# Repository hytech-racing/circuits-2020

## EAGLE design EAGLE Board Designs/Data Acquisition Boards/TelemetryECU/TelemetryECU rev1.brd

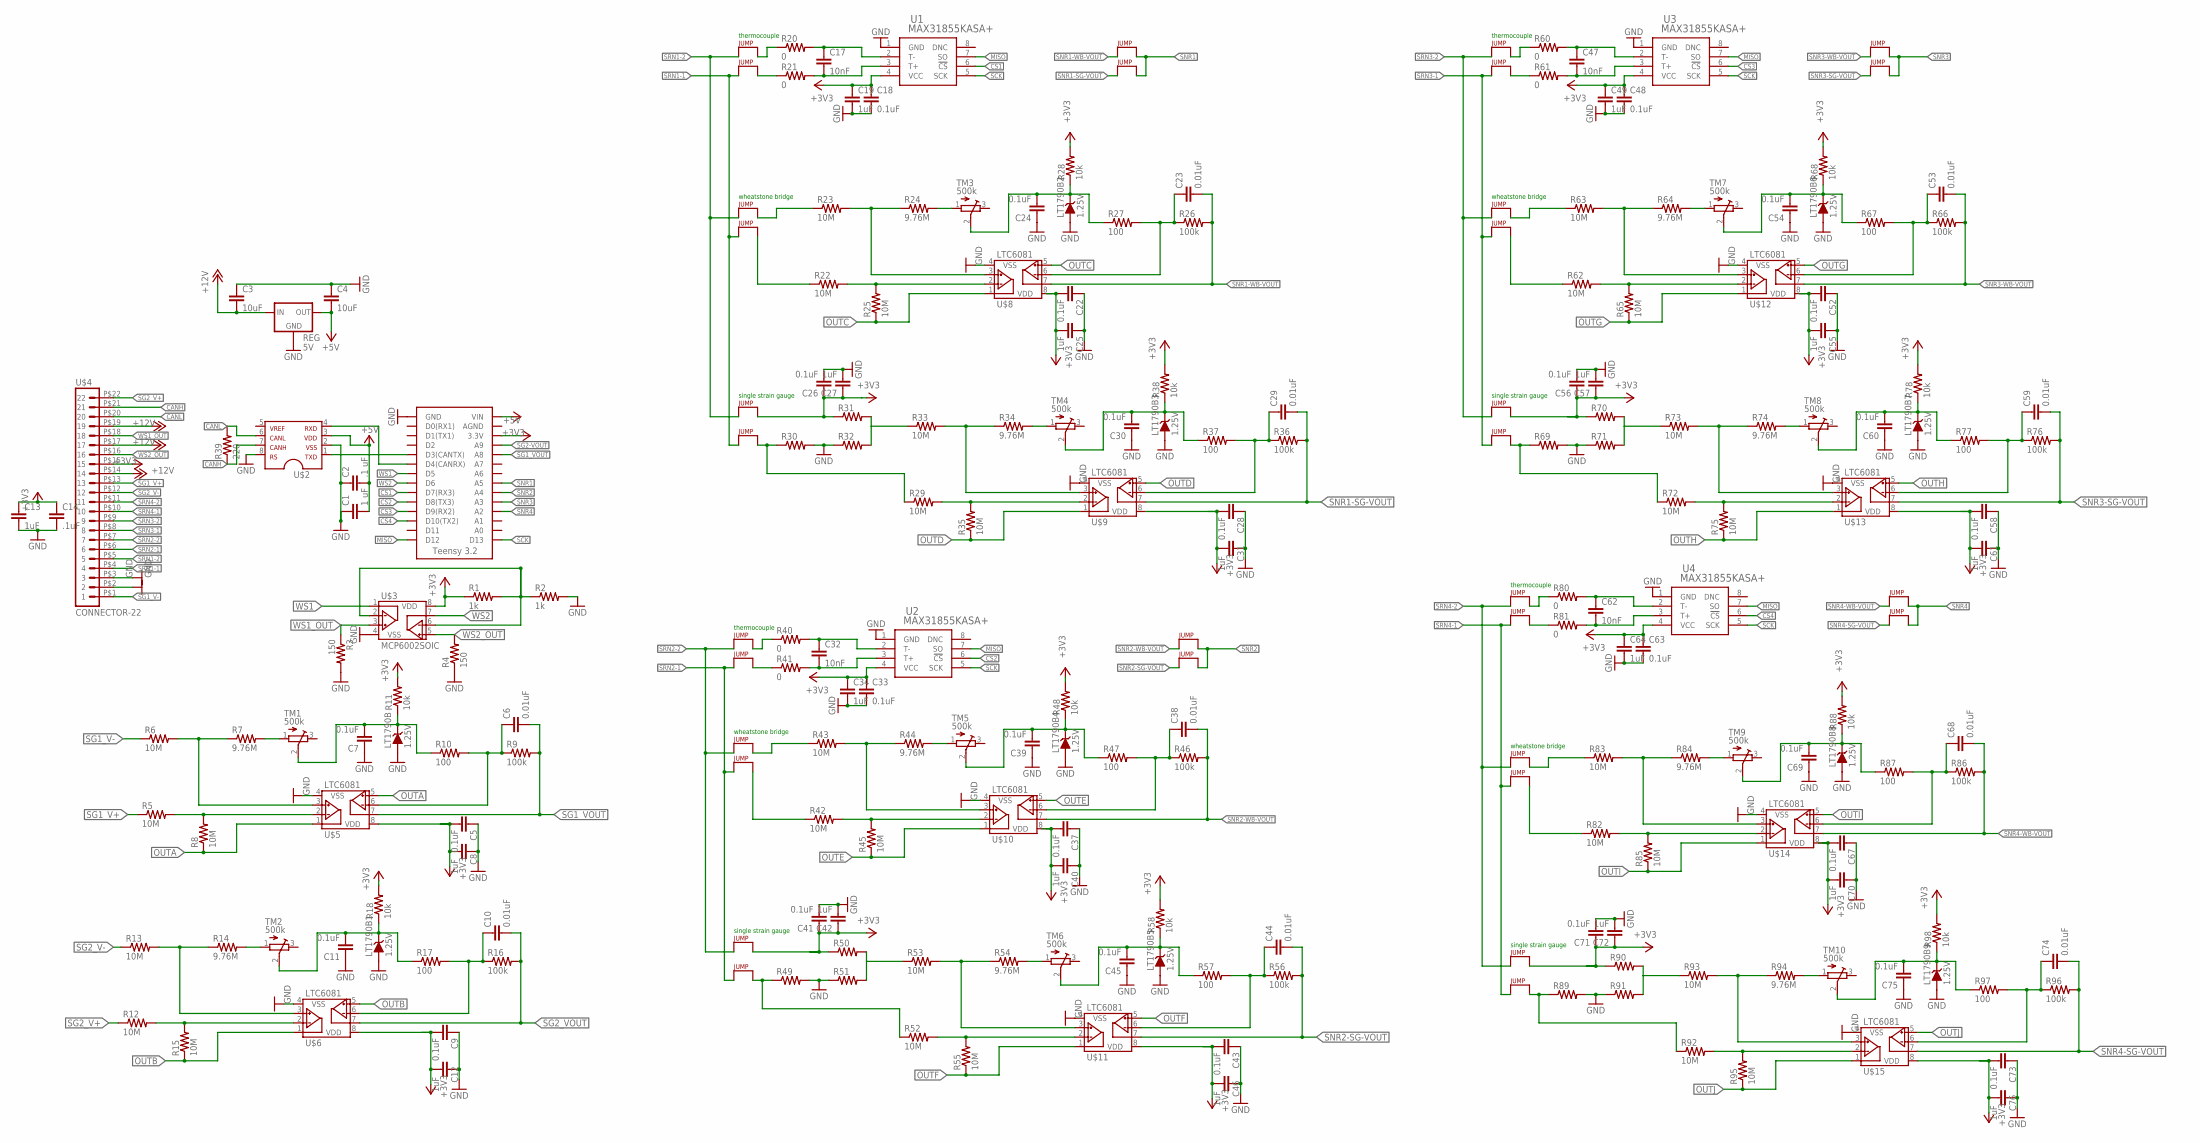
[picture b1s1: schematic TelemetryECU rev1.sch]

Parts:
C1: 1 uF; 0603-CAP
C2: .1 uF; 0603-CAP
C3, C4: 10uF; 0603-CAP
C5, C7, C9, C11, C18, C26, C33, C41, C48, C56, C63, C71: 0.1uF; 0603-CAP
C6, C10: 0.01uF; 0603-CAP
C8, C12, C13, C19, C27, C34, C42, C49, C57, C64, C72: 1uF; 0603-CAP
C14: .1uF; 0603-CAP
C17, C32, C47, C62: 10nF; 0603-CAP
C22, C24, C28, C30, C37, C39, C43, C45, C52, C54, C58, C60, C67, C69, C73, C75: 0.1uF; 0805
C23, C29, C38, C44, C53, C59, C68, C74: 0.01uF; 0805
C25, C31, C40, C46, C55, C61, C70, C76: 1uF; 0805
J1, J2, J5, J6, J7, J8, J9, J10, J13, J14, J15, J16, J17, J18, J21, J22, J23, J24, J25, J26, J29, J30, J31, J32, J34, J35, J37, J38, J40, J41, J42, J43: JUMPER.1; 1X02
LT1790B, LT1790B1, LT1790B2, LT1790B3, LT1790B4, LT1790B5, LT1790B6, LT1790B7, LT1790B8, LT1790B9: 1.25V; 0805_D
R1, R2: 1k; 0603-RES
R3, R4: 150; 0603-RES
R5, R6, R8, R12, R13, R15: 10M; 0603-RES
R7, R14: 9.76M; 0603-RES
R9, R16: 100k; 0603-RES
R10, R17: 100; 0603-RES
R11, R18: 10k; 0603-RES
R20, R21, R40, R41, R60, R61, R80, R81: 0; 0603-RES
R22, R23, R25, R29, R33, R35, R42, R43, R45, R52, R53, R55, R62, R63, R65, R72, R73, R75, R82, R83, R85, R92, R93, R95: 10M; 0805
R24, R34, R44, R54, R64, R74, R84, R94: 9.76M; 0805
R26, R36, R46, R56, R66, R76, R86, R96: 100k; 0805
R27, R37, R47, R57, R67, R77, R87, R97: 100; 0805
R28, R38, R48, R58, R68, R78, R88, R98: 10k; 0805
R30, R31, R32, R49, R50, R51, R69, R70, R71, R89, R90, R91: RESISTOR0603; 0603-RES
R39: 220; 0603-RES
REG: 5V; OKI-78SR
TM1, TM2, TM3, TM4, TM5, TM6, TM7, TM8, TM9, TM10: 500k; TC33X
U1, U2, U3, U4: MAX31855KASA+; 21-0041B_8
U$1: TEENSY_3.2_SIMPLE
U$2: MCP2551; SOIC-08
U$3: MCP6002SOIC; SOIC-08
U$4: CONNECTOR-22; AUTOSPORT_12-35
U$5, U$6, U$8, U$9, U$10, U$11, U$12, U$13, U$14, U$15: LTC6081; MSOP-8_MS

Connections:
+3V3: C5.2, C8.1, C9.2, C12.1, C13.1, C14.1, C18.1, C19.1, C22.2, C25.2, C26.1, C27.1, C28.2, C31.1, C33.1, C34.1, C37.2, C40.2, C41.1, C42.1, C43.2, C46.1, C48.1, C49.1, C52.2, C55.2, C56.1, C57.1, C58.2, C61.1, C63.1, C64.1, C67.2, C70.2, C71.1, C72.1, C73.2, C76.1, J7.2, J15.2, J23.2, J31.2, R1.1, R11.2, R18.2, R28.2, R31.1, R38.2, R48.2, R50.1, R58.2, R68.2, R70.1, R78.2, R88.2, R90.1, R98.2, U1.4 (VCC), U2.4 (VCC), U3.4 (VCC), U4.4 (VCC), U$1.3.3V, U$3.8 (VDD), U$4.P$15 (15), U$5.8 (VDD), U$6.8 (VDD), U$8.8 (VDD), U$9.8 (VDD), U$10.8 (VDD), U$11.8 (VDD), U$12.8 (VDD), U$13.8 (VDD), U$14.8 (VDD), U$15.8 (VDD)
+5V: C1.2, C2.2, C4.2, REG.3 (OUT), U$1.VIN, U$2.3
+12V: C3.2, REG.1 (IN), U$4.P$14 (14), U$4.P$17 (17), U$4.P$19 (19)
CANH: R39.1, U$2.7, U$4.P$21 (21)
CANL: R39.2, U$2.6, U$4.P$20 (20)
CS1: U1.6 (!CS), U$1.D7(RX3)
CS2: U2.6 (!CS), U$1.D8(TX3)
CS3: U3.6 (!CS), U$1.D9(RX2)
CS4: U4.6 (!CS), U$1.D10(TX2)
GND: C1.1, C2.1, C3.1, C4.1, C5.1, C7.1, C8.2, C9.1, C11.1, C12.2, C13.2, C14.2, C18.2, C19.2, C22.1, C24.1, C25.1, C26.2, C27.2, C28.1, C30.1, C31.2, C33.2, C34.2, C37.1, C39.1, C40.1, C41.2, C42.2, C43.1, C45.1, C46.2, C48.2, C49.2, C52.1, C54.1, C55.1, C56.2, C57.2, C58.1, C60.1, C61.2, C63.2, C64.2, C67.1, C69.1, C70.1, C71.2, C72.2, C73.1, C75.1, C76.2, LT1790B.A, LT1790B1.A, LT1790B2.A, LT1790B3.A, LT1790B4.A, LT1790B5.A, LT1790B6.A, LT1790B7.A, LT1790B8.A, LT1790B9.A, R2.2, R3.2, R4.1, R30.2, R32.1, R49.2, R51.1, R69.2, R71.1, R89.2, R91.1, REG.2 (GND), U1.1 (GND), U2.1 (GND), U3.1 (GND), U4.1 (GND), U$1.GND, U$2.2, U$2.8, U$3.4 (VSS), U$4.P$2 (2), U$4.P$3 (3), U$5.4 (VSS), U$6.4 (VSS), U$8.4 (VSS), U$9.4 (VSS), U$10.4 (VSS), U$11.4 (VSS), U$12.4 (VSS), U$13.4 (VSS), U$14.4 (VSS), U$15.4 (VSS)
INB-: C6.1, R9.1, R10.2, U$5.6 (VINB-)
INB-1: C10.1, R16.1, R17.2, U$6.6 (VINB-)
INB-2: C23.1, R26.1, R27.2, U$8.6 (VINB-)
INB-3: C29.1, R36.1, R37.2, U$9.6 (VINB-)
INB-4: C38.1, R46.1, R47.2, U$10.6 (VINB-)
INB-5: C44.1, R56.1, R57.2, U$11.6 (VINB-)
INB-6: C53.1, R66.1, R67.2, U$12.6 (VINB-)
INB-7: C59.1, R76.1, R77.2, U$13.6 (VINB-)
INB-8: C68.1, R86.1, R87.2, U$14.6 (VINB-)
INB-9: C74.1, R96.1, R97.2, U$15.6 (VINB-)
MISO: U1.7 (SO), U2.7 (SO), U3.7 (SO), U4.7 (SO), U$1.D12
unnamed: U$1.D4(CANRX), U$2.4
unnamed: C17.1, R20.2, U1.2 (T-)
unnamed: U$1.D3(CANTX), U$2.1
unnamed: R1.2, R2.1, U$3.2 (VINA-), U$3.6 (VINB-)
unnamed: R5.2, R8.2, U$5.2 (VINA-)
unnamed: C17.2, R21.2, U1.3 (T+)
unnamed: J2.2, R21.1
unnamed: R6.2, R7.1, U$5.3 (VINA+)
unnamed: C7.2, LT1790B.C, R10.1, R11.1, TM1.2 (S)
unnamed: R7.2, TM1.1 (A)
unnamed: R12.2, R15.2, U$6.2 (VINA-)
unnamed: R13.2, R14.1, U$6.3 (VINA+)
unnamed: C11.2, LT1790B1.C, R17.1, R18.1, TM2.2 (S)
unnamed: R14.2, TM2.1 (A)
unnamed: J1.2, R20.1
unnamed: R22.2, R25.2, U$8.2 (VINA-)
unnamed: R23.2, R24.1, U$8.3 (VINA+)
unnamed: C24.2, LT1790B2.C, R27.1, R28.1, TM3.2 (S)
unnamed: R24.2, TM3.1 (A)
unnamed: J6.2, R22.1
unnamed: R31.2, R32.2, R33.1
unnamed: J8.2, R29.1, R30.1
unnamed: C32.1, R40.2, U2.2 (T-)
unnamed: J5.2, R23.1
unnamed: R29.2, R35.2, U$9.2 (VINA-)
unnamed: R33.2, R34.1, U$9.3 (VINA+)
unnamed: C30.2, LT1790B3.C, R37.1, R38.1, TM4.2 (S)
unnamed: R34.2, TM4.1 (A)
unnamed: C32.2, R41.2, U2.3 (T+)
unnamed: J10.2, R41.1
unnamed: J9.2, R40.1
unnamed: R42.2, R45.2, U$10.2 (VINA-)
unnamed: R43.2, R44.1, U$10.3 (VINA+)
unnamed: C39.2, LT1790B4.C, R47.1, R48.1, TM5.2 (S)
unnamed: R44.2, TM5.1 (A)
unnamed: R50.2, R51.2, R53.1
unnamed: J16.2, R49.1, R52.1
unnamed: J14.2, R42.1
unnamed: J13.2, R43.1
unnamed: R52.2, R55.2, U$11.2 (VINA-)
unnamed: R53.2, R54.1, U$11.3 (VINA+)
unnamed: C45.2, LT1790B5.C, R57.1, R58.1, TM6.2 (S)
unnamed: R54.2, TM6.1 (A)
unnamed: C47.1, R60.2, U3.2 (T-)
unnamed: C47.2, R61.2, U3.3 (T+)
unnamed: J18.2, R61.1
unnamed: J17.2, R60.1
unnamed: R62.2, R65.2, U$12.2 (VINA-)
unnamed: R63.2, R64.1, U$12.3 (VINA+)
unnamed: C54.2, LT1790B6.C, R67.1, R68.1, TM7.2 (S)
unnamed: R64.2, TM7.1 (A)
unnamed: R70.2, R71.2, R73.1
unnamed: J24.2, R69.1, R72.1
unnamed: J22.2, R62.1
unnamed: J21.2, R63.1
unnamed: R72.2, R75.2, U$13.2 (VINA-)
unnamed: R73.2, R74.1, U$13.3 (VINA+)
unnamed: C60.2, LT1790B7.C, R77.1, R78.1, TM8.2 (S)
unnamed: R74.2, TM8.1 (A)
unnamed: C62.1, R80.2, U4.2 (T-)
unnamed: C62.2, R81.2, U4.3 (T+)
unnamed: J26.2, R81.1
unnamed: J25.2, R80.1
unnamed: R82.2, R85.2, U$14.2 (VINA-)
unnamed: R83.2, R84.1, U$14.3 (VINA+)
unnamed: C69.2, LT1790B8.C, R87.1, R88.1, TM9.2 (S)
unnamed: R84.2, TM9.1 (A)
unnamed: R90.2, R91.2, R93.1
unnamed: J32.2, R89.1, R92.1
unnamed: J30.2, R82.1
unnamed: J29.2, R83.1
unnamed: R92.2, R95.2, U$15.2 (VINA-)
unnamed: R93.2, R94.1, U$15.3 (VINA+)
unnamed: C75.2, LT1790B9.C, R97.1, R98.1, TM10.2 (S)
unnamed: R94.2, TM10.1 (A)
OUTA: R8.1, U$5.1 (VOUTA), U$5.5 (VINB+)
OUTB: R15.1, U$6.1 (VOUTA), U$6.5 (VINB+)
OUTC: R25.1, U$8.1 (VOUTA), U$8.5 (VINB+)
OUTD: R35.1, U$9.1 (VOUTA), U$9.5 (VINB+)
OUTE: R45.1, U$10.1 (VOUTA), U$10.5 (VINB+)
OUTF: R55.1, U$11.1 (VOUTA), U$11.5 (VINB+)
OUTG: R65.1, U$12.1 (VOUTA), U$12.5 (VINB+)
OUTH: R75.1, U$13.1 (VOUTA), U$13.5 (VINB+)
OUTI: R85.1, U$14.1 (VOUTA), U$14.5 (VINB+)
OUTJ: R95.1, U$15.1 (VOUTA), U$15.5 (VINB+)
SCK: U1.5 (SCK), U2.5 (SCK), U3.5 (SCK), U4.5 (SCK), U$1.D13
SG1_V+: R5.1, U$4.P$13 (13)
SG1_V-: R6.1, U$4.P$1 (1)
SG1_VOUT: C6.2, R9.2, U$1.A8, U$5.7 (VOUTB)
SG2-VOUT: U$1.A9
SG2_V+: R12.1, U$4.P$22 (22)
SG2_V-: R13.1, U$4.P$12 (12)
SG2_VOUT: C10.2, R16.2, U$6.7 (VOUTB)
SNR1: J34.2, J35.2, U$1.A5
SNR1-SG-VOUT: C29.2, J35.1, R36.2, U$9.7 (VOUTB)
SNR1-WB-VOUT: C23.2, J34.1, R26.2, U$8.7 (VOUTB)
SNR2: J42.2, J43.2, U$1.A4
SNR2-SG-VOUT: C44.2, J42.1, R56.2, U$11.7 (VOUTB)
SNR2-WB-VOUT: C38.2, J43.1, R46.2, U$10.7 (VOUTB)
SNR3: J37.2, J38.2, U$1.A3
SNR3-SG-VOUT: C59.2, J38.1, R76.2, U$13.7 (VOUTB)
SNR3-WB-VOUT: C53.2, J37.1, R66.2, U$12.7 (VOUTB)
SNR4: J40.2, J41.2, U$1.A2
SNR4-SG-VOUT: C74.2, J41.1, R96.2, U$15.7 (VOUTB)
SNR4-WB-VOUT: C68.2, J40.1, R86.2, U$14.7 (VOUTB)
SRN1-1: J2.1, J6.1, J8.1, U$4.P$4 (4)
SRN1-2: J1.1, J5.1, J7.1, U$4.P$5 (5)
SRN2-1: J10.1, J14.1, J16.1, U$4.P$6 (6)
SRN2-2: J9.1, J13.1, J15.1, U$4.P$7 (7)
SRN3-1: J18.1, J22.1, J24.1, U$4.P$8 (8)
SRN3-2: J17.1, J21.1, J23.1, U$4.P$9 (9)
SRN4-1: J26.1, J30.1, J32.1, U$4.P$10 (10)
SRN4-2: J25.1, J29.1, J31.1, U$4.P$11 (11)
WS1: U$1.D5, U$3.1 (VOUTA)
WS1_OUT: R3.1, U$3.3 (VINA+), U$4.P$18 (18)
WS2: U$1.D6, U$3.7 (VOUTB)
WS2_OUT: R4.2, U$3.5 (VINB+), U$4.P$16 (16)

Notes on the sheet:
thermocouple
wheatstone bridge
single strain gauge

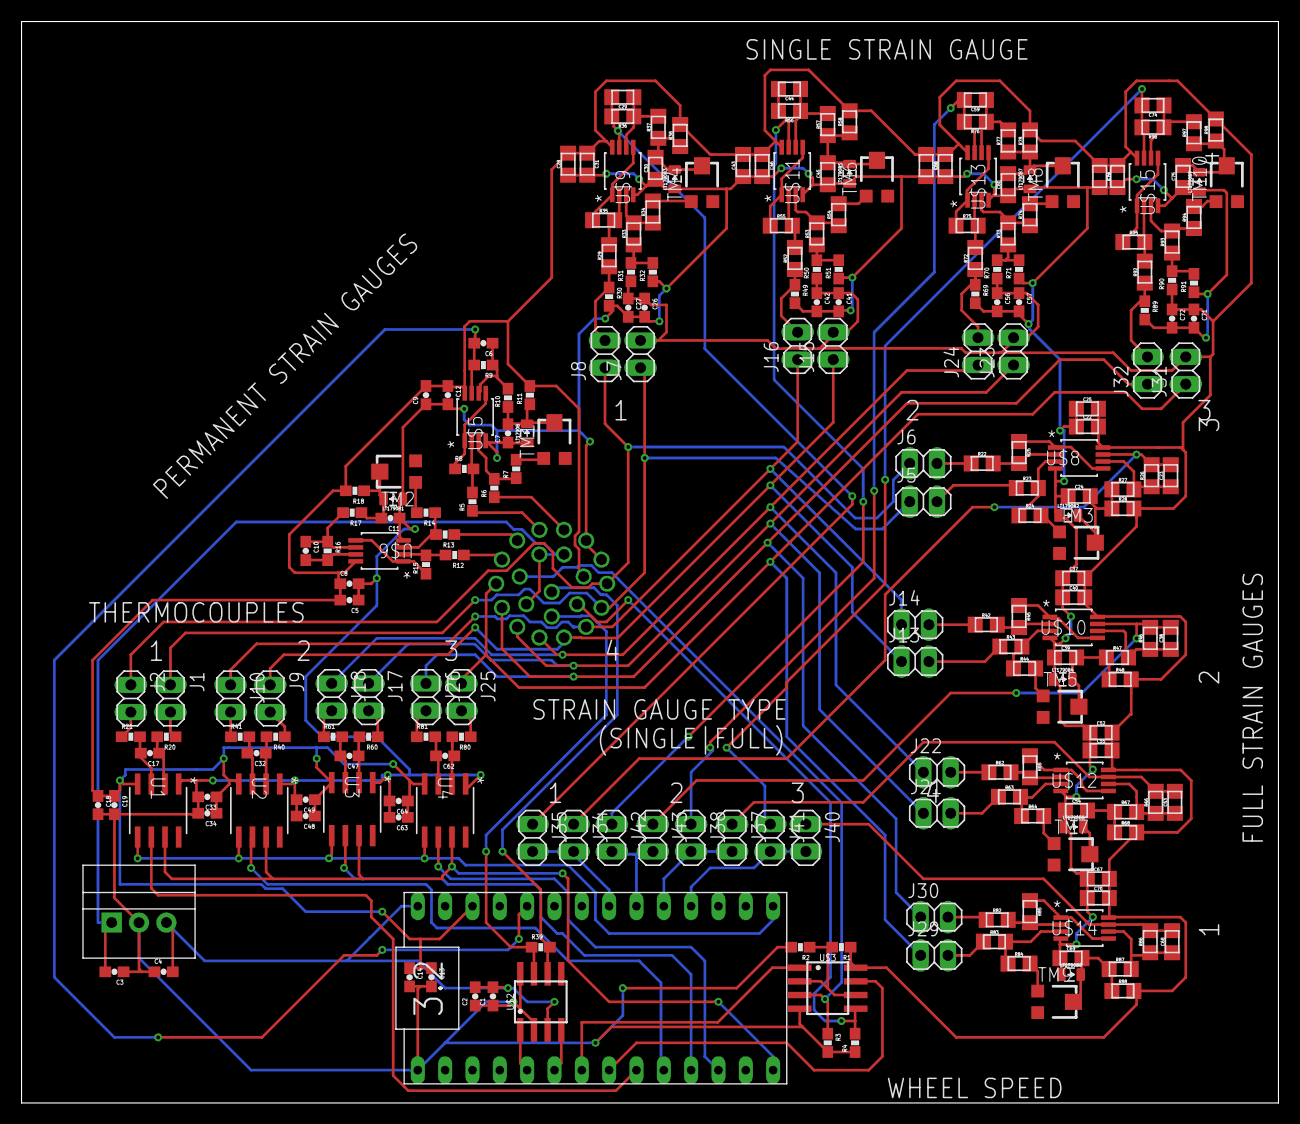
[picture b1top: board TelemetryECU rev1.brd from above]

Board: 2 copper layers, 116.8 x 100.5 mm, 232 parts (0 on the bottom side), 137 nets.

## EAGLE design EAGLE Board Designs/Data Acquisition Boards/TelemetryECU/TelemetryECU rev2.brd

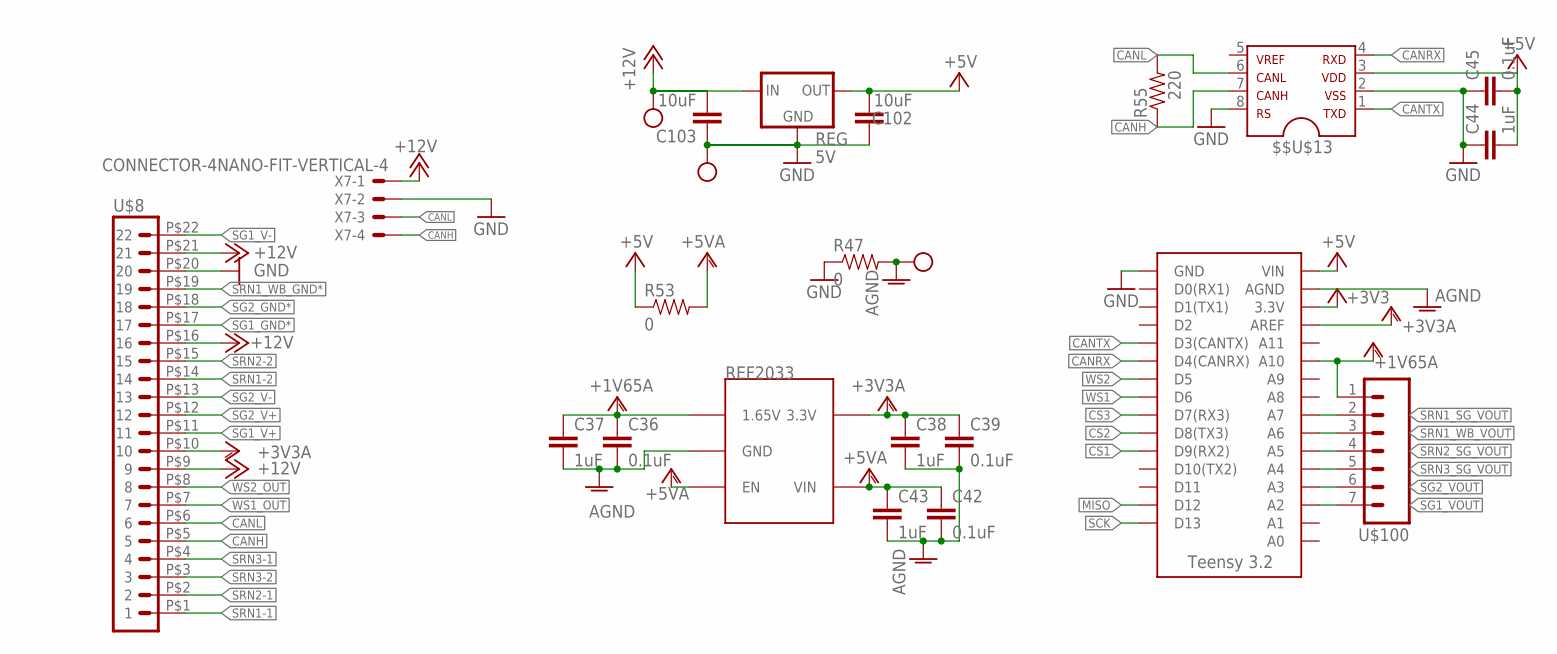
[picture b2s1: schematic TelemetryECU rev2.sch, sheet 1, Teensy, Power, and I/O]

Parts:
$$U$11: TEST_POINT
$$U$13: MCP2551; SOIC-08
C36, C39, C42, C45: 0.1uF; 0603-CAP
C37, C38, C43, C44: 1uF; 0603-CAP
C102, C103: 10uF; 0603-CAP
R47, R53: 0; 0603-RES
R55: 220; 0603-RES
REG: 5V; OKI-78SR
U$7: REF2033; SOT-23-5
U$8: CONNECTOR-22; AUTOSPORT_12-35
U$9, U$10: TEST_POINT
U$14: TEENSY_3.2_EXT_12ANALOG_AREF
U$100: M07; 1X07
X7: CONNECTOR-4NANO-FIT-VERTICAL-4; NANO-FIT_VERTICAL-4

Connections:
+1V65A: C36.1, C37.1, U$7.1 (1.65V), U$14.A10, U$100.1; also elsewhere on the board
+3V3: U$14.3.3V; also elsewhere on the board
+3V3A: C38.1, C39.1, U$7.5 (3.3V), U$8.P$10 (10), U$14.AREF; also elsewhere on the board
+5V: $$U$13.3, C44.2, C45.2, C102.2, R53.1, REG.3 (OUT), U$14.VIN
+5VA: C42.1, C43.1, R53.2, U$7.3 (EN), U$7.4 (VIN); also elsewhere on the board
+12V: C103.2, REG.1 (IN), U$8.P$9 (9), U$8.P$16 (16), U$8.P$21 (21), U$10.P$1, X7.P$1
AGND: $$U$11.P$1, C36.2, C37.2, C38.2, C39.2, C42.2, C43.2, R47.2, U$7.2 (GND), U$14.AGND; also elsewhere on the board
CANH: $$U$13.7, R55.1, U$8.P$5 (5), X7.P$4
CANL: $$U$13.6, R55.2, U$8.P$6 (6), X7.P$3
CANRX: $$U$13.4, U$14.D4(CANRX)
CANTX: $$U$13.1, U$14.D3(CANTX)
CS1: U$14.D9(RX2); also elsewhere on the board
CS2: U$14.D8(TX3); also elsewhere on the board
CS3: U$14.D7(RX3); also elsewhere on the board
GND: $$U$13.2, $$U$13.8, C44.1, C45.1, C102.1, C103.1, R47.1, REG.2 (GND), U$8.P$20 (20), U$9.P$1, U$14.GND, X7.P$2; also elsewhere on the board
MISO: U$14.D12; also elsewhere on the board
SCK: U$14.D13; also elsewhere on the board
SG1_GND*: U$8.P$17 (17); also elsewhere on the board
SG1_V+: U$8.P$11 (11); also elsewhere on the board
SG1_V-: U$8.P$22 (22); also elsewhere on the board
SG1_VOUT: U$14.A2, U$100.7; also elsewhere on the board
SG2_GND*: U$8.P$18 (18); also elsewhere on the board
SG2_V+: U$8.P$12 (12); also elsewhere on the board
SG2_V-: U$8.P$13 (13); also elsewhere on the board
SG2_VOUT: U$14.A3, U$100.6; also elsewhere on the board
SRN1-1: U$8.P$1 (1); also elsewhere on the board
SRN1-2: U$8.P$14 (14); also elsewhere on the board
SRN1_SG_VOUT: U$14.A7, U$100.2; also elsewhere on the board
SRN1_WB_GND*: U$8.P$19 (19); also elsewhere on the board
SRN1_WB_VOUT: U$14.A6, U$100.3; also elsewhere on the board
SRN2-1: U$8.P$2 (2); also elsewhere on the board
SRN2-2: U$8.P$15 (15); also elsewhere on the board
SRN2_SG_VOUT: U$14.A5, U$100.4; also elsewhere on the board
SRN3-1: U$8.P$4 (4); also elsewhere on the board
SRN3-2: U$8.P$3 (3); also elsewhere on the board
SRN3_SG_VOUT: U$14.A4, U$100.5; also elsewhere on the board
WS1: U$14.D6; also elsewhere on the board
WS1_OUT: U$8.P$7 (7); also elsewhere on the board
WS2: U$14.D5; also elsewhere on the board
WS2_OUT: U$8.P$8 (8); also elsewhere on the board

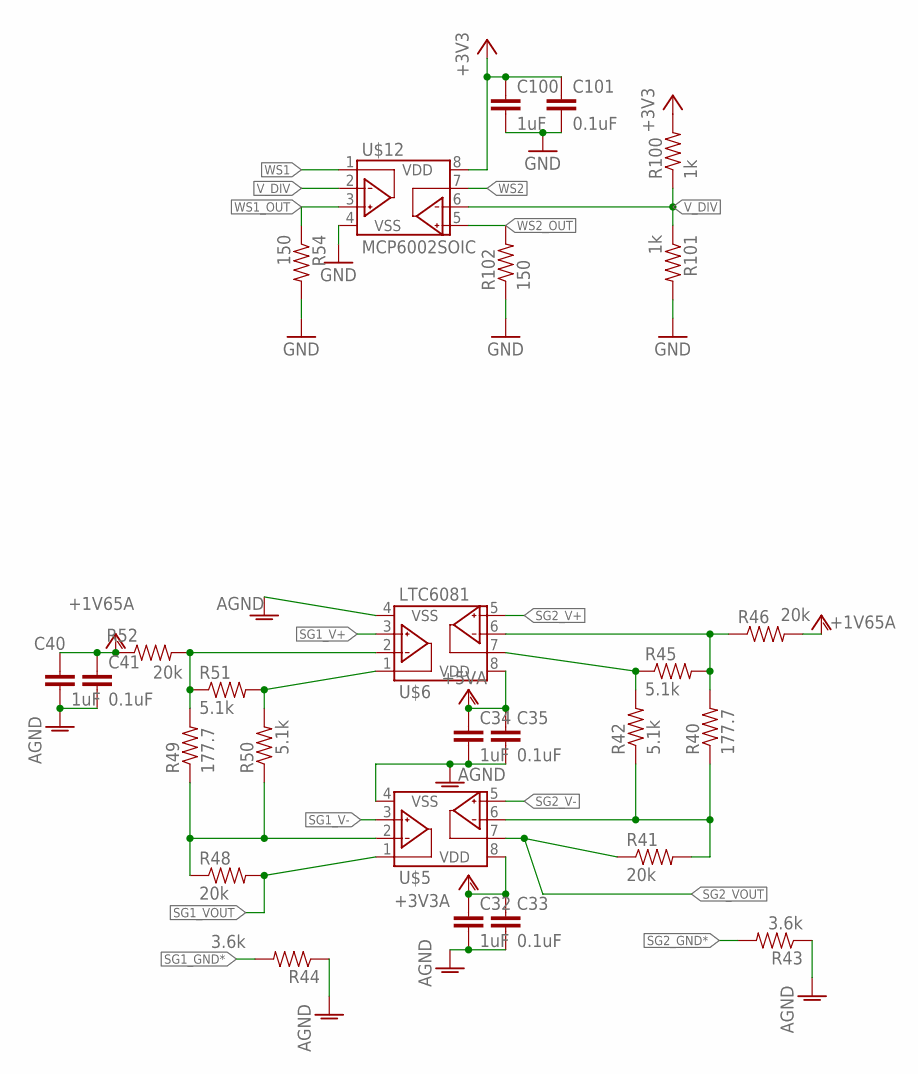
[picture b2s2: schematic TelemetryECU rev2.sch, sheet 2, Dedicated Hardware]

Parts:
C32, C34, C40, C100: 1uF; 0603-CAP
C33, C35, C41, C101: 0.1uF; 0603-CAP
R40, R49: 177.7; 0603-RES
R41, R46, R48, R52: 20k; 0603-RES
R42, R45, R50, R51: 5.1k; 0603-RES
R43, R44: 3.6k; 0603-RES
R54, R102: 150; 0603-RES
R100, R101: 1k; 0603-RES
U$5, U$6: LTC6081; MSOP-8_MS
U$12: MCP6002SOIC; SOIC-08

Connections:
+1V65A: C40.1, C41.1, R46.2, R52.1; also elsewhere on the board
+3V3: C100.1, C101.1, R100.2, U$12.8 (VDD); also elsewhere on the board
+3V3A: C32.1, C33.1, U$5.8 (VDD); also elsewhere on the board
+5VA: C34.1, C35.1, U$6.8 (VDD); also elsewhere on the board
AGND: C32.2, C33.2, C34.2, C35.2, C40.2, C41.2, R43.1, R44.1, U$5.4 (VSS), U$6.4 (VSS); also elsewhere on the board
GND: C100.2, C101.2, R54.2, R101.2, R102.1, U$12.4 (VSS); also elsewhere on the board
unnamed: R50.2, R51.2, U$6.1 (VOUTA)
unnamed: R49.2, R51.1, R52.2, U$6.2 (VINA-)
unnamed: R40.2, R45.2, R46.1, U$6.6 (VINB-)
unnamed: R48.1, R49.1, R50.1, U$5.2 (VINA-)
unnamed: R42.2, R45.1, U$6.7 (VOUTB)
unnamed: R40.1, R41.2, R42.1, U$5.6 (VINB-)
SG1_GND*: R44.2; also elsewhere on the board
SG1_V+: U$6.3 (VINA+); also elsewhere on the board
SG1_V-: U$5.3 (VINA+); also elsewhere on the board
SG1_VOUT: R48.2, U$5.1 (VOUTA); also elsewhere on the board
SG2_GND*: R43.2; also elsewhere on the board
SG2_V+: U$6.5 (VINB+); also elsewhere on the board
SG2_V-: U$5.5 (VINB+); also elsewhere on the board
SG2_VOUT: R41.1, U$5.7 (VOUTB); also elsewhere on the board
V_DIV: R100.1, R101.1, U$12.2 (VINA-), U$12.6 (VINB-)
WS1: U$12.1 (VOUTA); also elsewhere on the board
WS1_OUT: R54.1, U$12.3 (VINA+); also elsewhere on the board
WS2: U$12.7 (VOUTB); also elsewhere on the board
WS2_OUT: R102.2, U$12.5 (VINB+); also elsewhere on the board

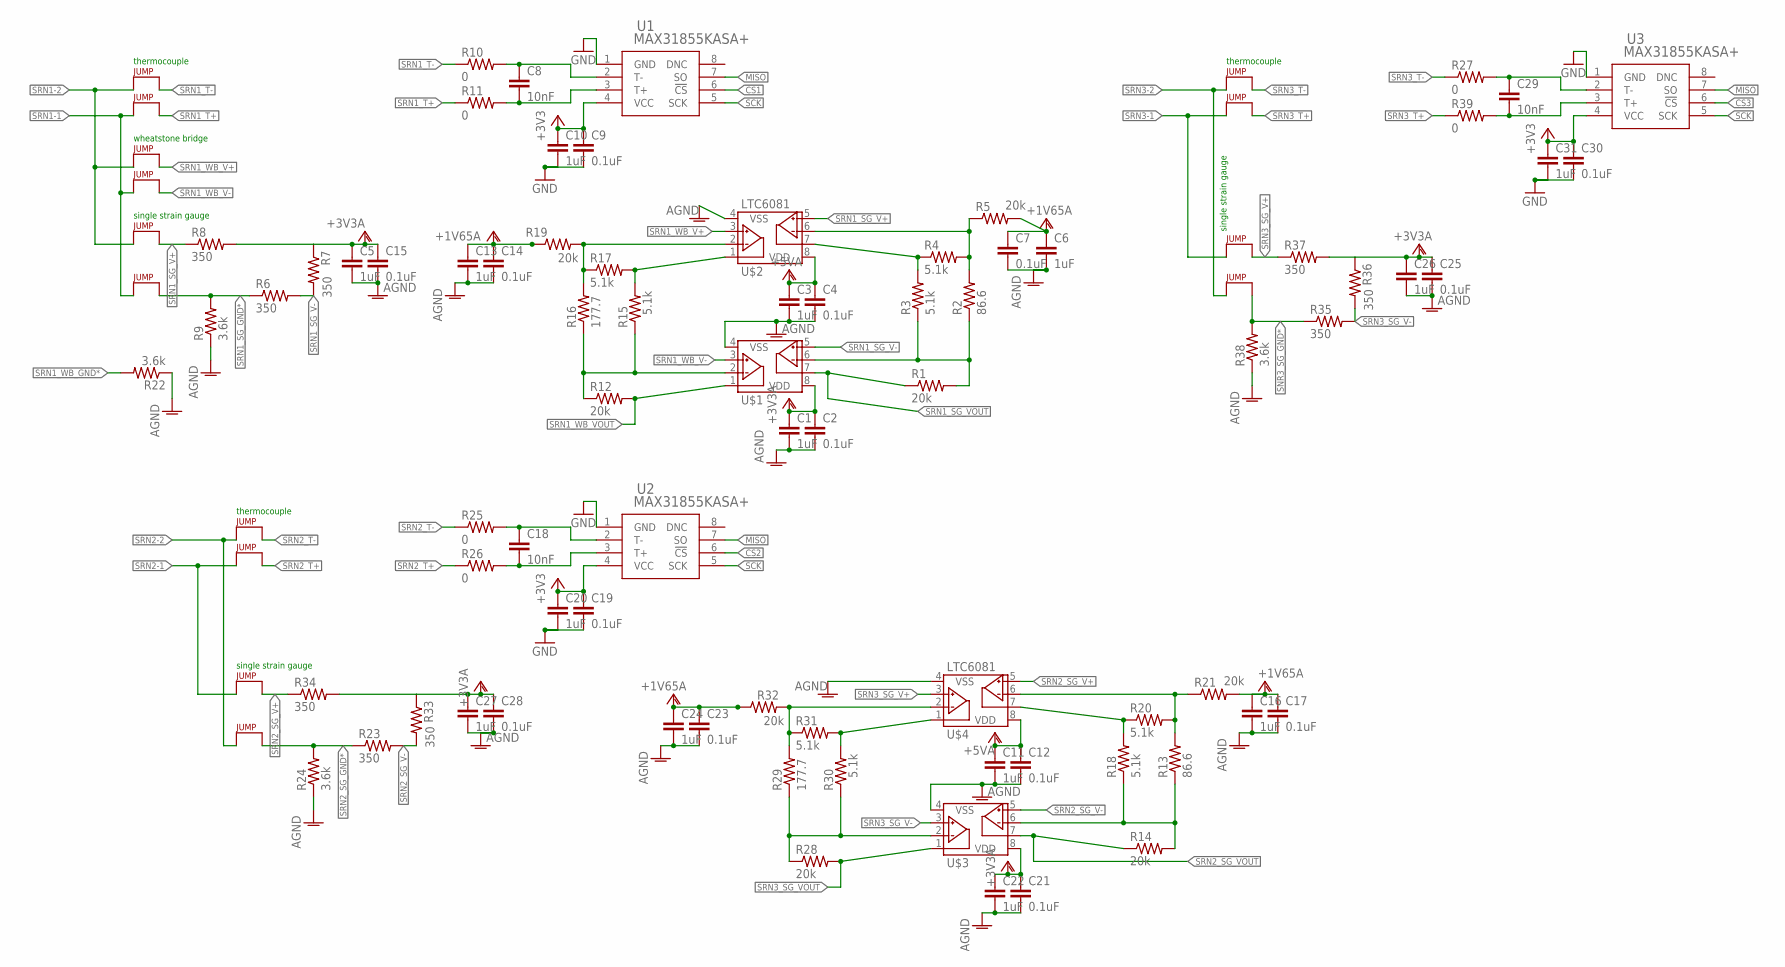
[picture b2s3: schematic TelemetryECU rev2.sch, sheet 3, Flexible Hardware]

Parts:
C1, C3, C5, C6, C10, C11, C13, C16, C20, C22, C24, C26, C27, C31: 1uF; 0603-CAP
C2, C4, C7, C9, C12, C14, C15, C17, C19, C21, C23, C25, C28, C30: 0.1uF; 0603-CAP
C8, C18, C29: 10nF; 0603-CAP
J1, J2, J3, J4, J5, J6, J7, J8, J9, J10, J11, J12, J13, J14: JUMPER.1; 1X02
R1, R5, R12, R14, R19, R21, R28, R32: 20k; 0603-RES
R2, R13: 86.6; 0603-RES
R3, R4, R15, R17, R18, R20, R30, R31: 5.1k; 0603-RES
R6, R7, R8, R23, R33, R34, R35, R36, R37: 350; 0603-RES
R9, R22, R24, R38: 3.6k; 0603-RES
R10, R11, R25, R26, R27, R39: 0; 0603-RES
R16, R29: 177.7; 0603-RES
U1, U2, U3: MAX31855KASA+; 21-0041B_8
U$1, U$2, U$3, U$4: LTC6081; MSOP-8_MS

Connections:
+1V65A: C6.1, C7.1, C13.1, C14.1, C16.1, C17.1, C23.1, C24.1, R5.2, R19.1, R21.2, R32.1; also elsewhere on the board
+3V3: C9.1, C10.1, C19.1, C20.1, C30.1, C31.1, U1.4 (VCC), U2.4 (VCC), U3.4 (VCC); also elsewhere on the board
+3V3A: C1.1, C2.1, C5.1, C15.1, C21.1, C22.1, C25.1, C26.1, C27.1, C28.1, R7.1, R8.2, R33.1, R34.2, R36.1, R37.2, U$1.8 (VDD), U$3.8 (VDD); also elsewhere on the board
+5VA: C3.1, C4.1, C11.1, C12.1, U$2.8 (VDD), U$4.8 (VDD); also elsewhere on the board
AGND: C1.2, C2.2, C3.2, C4.2, C5.2, C6.2, C7.2, C11.2, C12.2, C13.2, C14.2, C15.2, C16.2, C17.2, C21.2, C22.2, C23.2, C24.2, C25.2, C26.2, C27.2, C28.2, R9.1, R22.1, R24.1, R38.1, U$1.4 (VSS), U$2.4 (VSS), U$3.4 (VSS), U$4.4 (VSS); also elsewhere on the board
CS1: U1.6 (!CS); also elsewhere on the board
CS2: U2.6 (!CS); also elsewhere on the board
CS3: U3.6 (!CS); also elsewhere on the board
GND: C9.2, C10.2, C19.2, C20.2, C30.2, C31.2, U1.1 (GND), U2.1 (GND), U3.1 (GND); also elsewhere on the board
MISO: U1.7 (SO), U2.7 (SO), U3.7 (SO); also elsewhere on the board
unnamed: C8.1, R10.2, U1.2 (T-)
unnamed: C8.2, R11.2, U1.3 (T+)
unnamed: R16.2, R17.1, R19.2, U$2.2 (VINA-)
unnamed: R2.2, R4.2, R5.1, U$2.6 (VINB-)
unnamed: R15.2, R17.2, U$2.1 (VOUTA)
unnamed: R12.1, R15.1, R16.1, U$1.2 (VINA-)
unnamed: R3.2, R4.1, U$2.7 (VOUTB)
unnamed: C18.1, R25.2, U2.2 (T-)
unnamed: C18.2, R26.2, U2.3 (T+)
unnamed: R29.2, R31.1, R32.2, U$4.2 (VINA-)
unnamed: R13.2, R20.2, R21.1, U$4.6 (VINB-)
unnamed: R30.2, R31.2, U$4.1 (VOUTA)
unnamed: R28.1, R29.1, R30.1, U$3.2 (VINA-)
unnamed: R18.2, R20.1, U$4.7 (VOUTB)
unnamed: R13.1, R14.2, R18.1, U$3.6 (VINB-)
unnamed: C29.1, R27.2, U3.2 (T-)
unnamed: C29.2, R39.2, U3.3 (T+)
unnamed: R1.2, R2.1, R3.1, U$1.6 (VINB-)
SCK: U1.5 (SCK), U2.5 (SCK), U3.5 (SCK); also elsewhere on the board
SNR3_SG_GND*: J12.2, R35.1, R38.2
SRN1-1: J2.1, J5.1, J6.1; also elsewhere on the board
SRN1-2: J1.1, J3.1, J4.1; also elsewhere on the board
SRN1_SG_GND*: J2.2, R6.1, R9.2
SRN1_SG_V+: J1.2, R8.1, U$2.5 (VINB+)
SRN1_SG_V-: R6.2, R7.2, U$1.5 (VINB+)
SRN1_SG_VOUT: R1.1, U$1.7 (VOUTB); also elsewhere on the board
SRN1_T+: J5.2, R11.1
SRN1_T-: J4.2, R10.1
SRN1_WB_GND*: R22.2; also elsewhere on the board
SRN1_WB_V+: J3.2, U$2.3 (VINA+)
SRN1_WB_V-: J6.2, U$1.3 (VINA+)
SRN1_WB_VOUT: R12.2, U$1.1 (VOUTA); also elsewhere on the board
SRN2-1: J8.1, J10.1; also elsewhere on the board
SRN2-2: J7.1, J9.1; also elsewhere on the board
SRN2_SG_GND*: J7.2, R23.1, R24.2
SRN2_SG_V+: J8.2, R34.1, U$4.5 (VINB+)
SRN2_SG_V-: R23.2, R33.2, U$3.5 (VINB+)
SRN2_SG_VOUT: R14.1, U$3.7 (VOUTB); also elsewhere on the board
SRN2_T+: J10.2, R26.1
SRN2_T-: J9.2, R25.1
SRN3-1: J13.1, J14.1; also elsewhere on the board
SRN3-2: J11.1, J12.1; also elsewhere on the board
SRN3_SG_V+: J13.2, R37.1, U$4.3 (VINA+)
SRN3_SG_V-: R35.2, R36.2, U$3.3 (VINA+)
SRN3_SG_VOUT: R28.2, U$3.1 (VOUTA); also elsewhere on the board
SRN3_T+: J14.2, R39.1
SRN3_T-: J11.2, R27.1

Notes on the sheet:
thermocouple
wheatstone bridge
single strain gauge

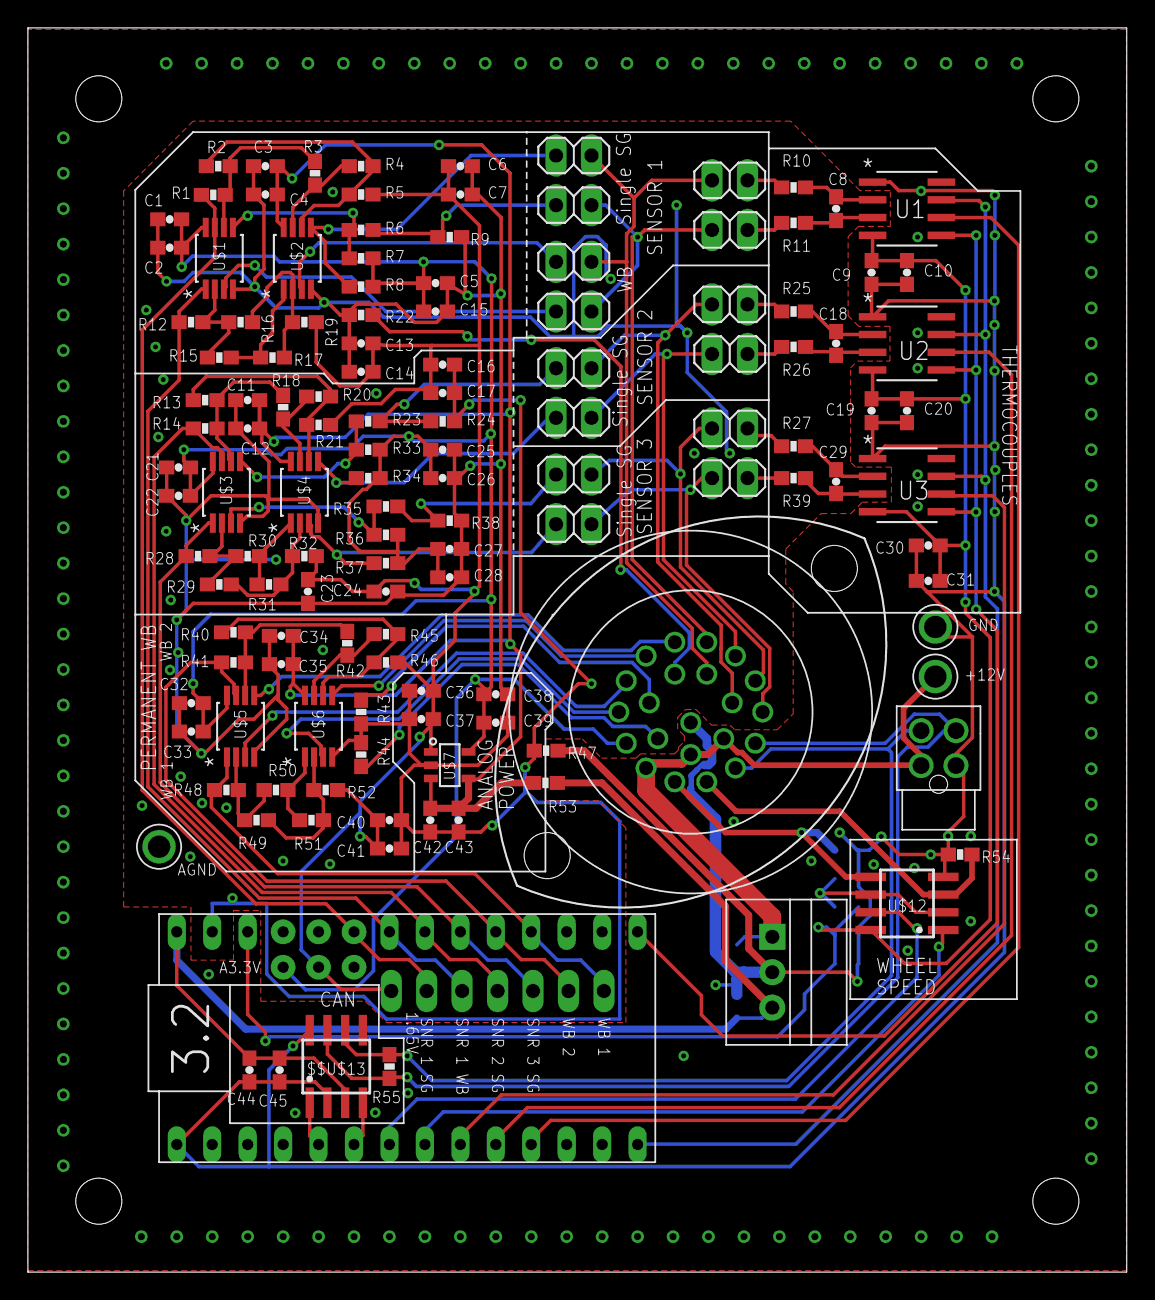
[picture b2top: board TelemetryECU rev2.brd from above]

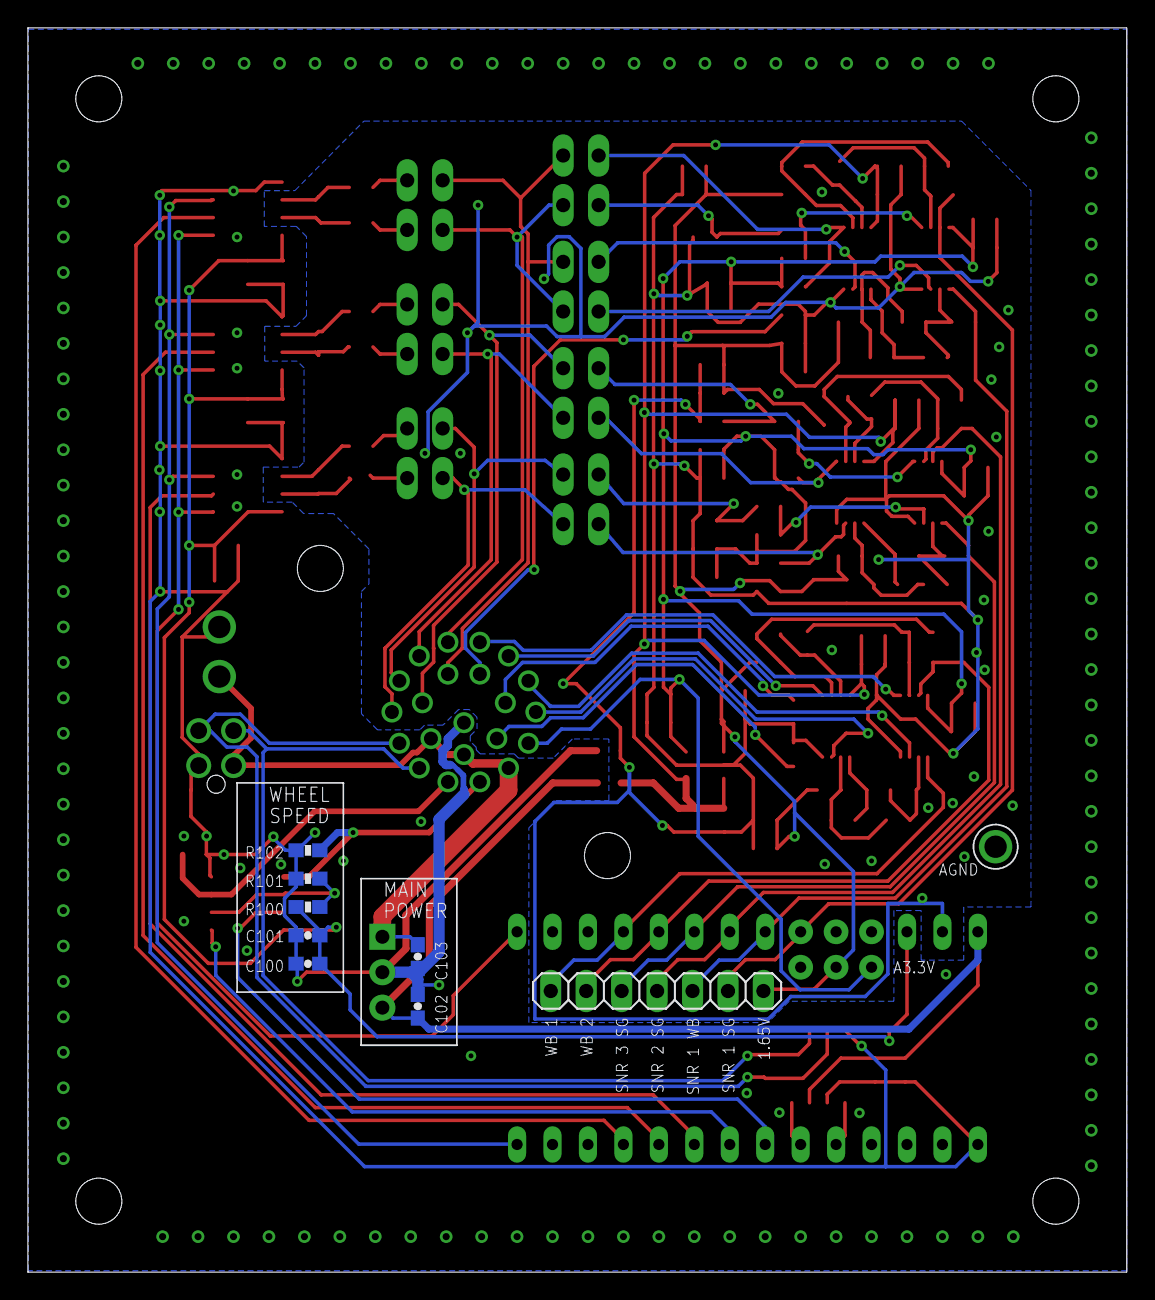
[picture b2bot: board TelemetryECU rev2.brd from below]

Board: 2 copper layers, 78.7 x 89.2 mm, 141 parts (8 on the bottom side), 82 nets.

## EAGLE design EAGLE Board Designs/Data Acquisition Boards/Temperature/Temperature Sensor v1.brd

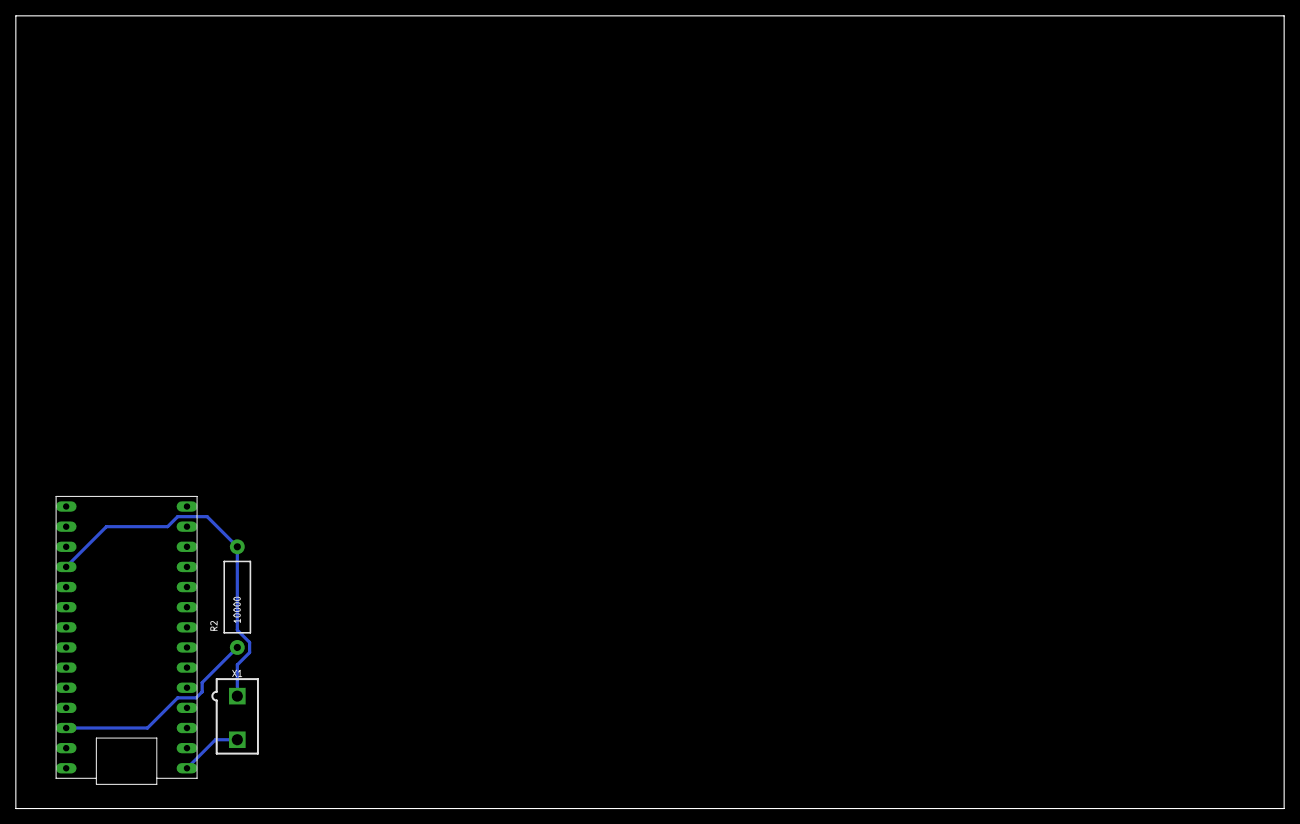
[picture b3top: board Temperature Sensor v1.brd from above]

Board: 2 copper layers, 160.0 x 100.0 mm, 3 parts (0 on the bottom side), 3 nets.

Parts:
R2: 10000; AXIAL-0.5
U$1: TEENSY_3.2_SIMPLE
X1: CONNECTOR-2; MINIFIT_5566-2

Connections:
unnamed: R2.P$1, U$1.3.3V
unnamed: R2.P$2, U$1.A2, X1.1
unnamed: U$1.GND, X1.2

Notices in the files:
parts and their libraries:
SparkFun-AnalogIC: Licensing:Creative Commons ShareAlike 4.0 International - https://creativecommons.org/licenses/by-sa/4.0
